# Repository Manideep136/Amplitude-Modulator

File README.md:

# Amplitude-Modulator

📌 Project Overview

This project is an Amplitude Modulator (AM) circuit designed and implemented as a PCB using KiCad.

Amplitude modulation is a technique used in communication systems where the amplitude of a high-frequency carrier signal is varied according to the amplitude of a lower-frequency message signal.

The purpose of this project is to understand the basic concept of AM and implement a simple amplitude modulation circuit using electronic components.

🎯 Objectives
Understand the basic concept of amplitude modulation.
Generate a carrier signal and message signal.
Combine the signals to produce an AM waveform.
Design the AM circuit schematic in KiCad.
Assign appropriate footprints to components.
Create a PCB layout.
Route the PCB tracks.
Perform ERC and DRC checks.
Visualize the completed PCB using KiCad 3D Viewer.
📡 What is Amplitude Modulation?

Amplitude Modulation (AM) is a modulation technique in which the amplitude of a carrier signal is changed according to the message signal, while the carrier frequency remains constant.

In simple terms:

Message Signal + Carrier Signal
              │
              ▼
       AM Modulator Circuit
              │
              ▼
          AM Output

The message signal contains the information, while the carrier signal is a higher-frequency signal used to carry that information.

⚙️ Working Principle

The amplitude modulator takes two input signals:

Message signal – the information signal.
Carrier signal – a high-frequency signal.

The modulator combines these signals and produces an amplitude-modulated output.

The basic AM equation is:

s(t) = Ac [1 + μ cos(ωm t)] cos(ωc t)

Where:

Ac = Carrier amplitude
μ = Modulation index
ωm = Message signal angular frequency
ωc = Carrier signal angular frequency

The frequency of the carrier remains constant, while its amplitude changes according to the message signal.

🧩 Components Used

The exact components depend on the circuit implementation. A typical AM modulator PCB may contain:

Reference	Component	Quantity
Q1	Transistor / Modulator Device	1
R1–R4	Resistors	As required
C1–C3	Capacitors	As required
J1	Message Signal Input	1
J2	Carrier Signal Input	1
J3	AM Output	1
VCC	DC Power Supply	1

Component values should be selected according to the actual schematic used in the project.

🔌 Inputs and Outputs
Message Input

The low-frequency information signal is connected to the message input.

Message Signal
      │
      ▼
   AM Circuit
Carrier Input

The high-frequency carrier signal is supplied to the carrier input.

Carrier Signal
      │
      ▼
   AM Circuit
AM Output

The resulting amplitude-modulated signal is available at the output connector.

Message + Carrier
       │
       ▼
 AM Modulator
       │
       ▼
   AM Output
🖥️ KiCad Design

The complete circuit was designed using KiCad.

Design Process
Create a new KiCad project.
Create the AM modulator schematic.
Add the required components.
Connect the components according to the circuit.
Add power connections.
Assign footprints.
Transfer the schematic to PCB Editor.
Place the components.
Route the PCB tracks.
Check the design using ERC.
Check the PCB using DRC.
View the final PCB using the 3D Viewer.

🔍 PCB Design Considerations

When designing the AM PCB, special attention should be given to:

Short signal paths.
Proper grounding.
Correct component placement.
Avoiding unnecessary long tracks.
Keeping the carrier signal path clean.
Proper separation of input and output signals.
Correct footprint selection.
Appropriate PCB track widths.

Since AM circuits can work with relatively higher-frequency signals, good PCB layout practices help reduce unwanted noise and interference.

🧪 Testing

After completing the PCB:

Check all component values.
Verify component orientation.
Check transistor pin configuration if a transistor is used.
Check capacitor polarity for polarized capacitors.
Verify the power supply connections.
Run ERC in KiCad.
Run DRC in KiCad.
Check the PCB for shorts.
Apply the required DC supply.
Connect the message signal.
Connect the carrier signal.
Observe the output using an oscilloscope.

The oscilloscope should show an AM waveform whose envelope follows the message signal.

📈 Modulation Index

The modulation index indicates how strongly the carrier is being modulated.

It can be calculated from the AM waveform as:

μ = (Vmax - Vmin) / (Vmax + Vmin)

Where:

Vmax = Maximum envelope amplitude
Vmin = Minimum envelope amplitude

For normal AM operation:

0 ≤ μ ≤ 1

If the modulation index becomes greater than 1, over-modulation can occur, which causes distortion.

✅ Advantages
Simple concept and easy to understand.
Useful for learning communication-system fundamentals.
Easy to observe using an oscilloscope.
Demonstrates the relationship between message and carrier signals.
Can be extended into a complete communication system.
⚠️ Limitations
AM is less power-efficient than some modern modulation techniques.
A significant amount of power can be present in the carrier.
It is susceptible to noise.
Over-modulation can cause distortion.
Practical performance depends on the circuit design and component selection.
🚀 Future Improvements

The project can be improved by adding:

Adjustable modulation depth.
Variable carrier frequency.
Signal amplification stage.
RF output stage.
LC filtering.
Audio input connector.
Oscilloscope test points.
Demodulator circuit.
Complete AM transmitter and receiver.
📚 Learning Outcomes

Through this project, I learned:

Basic principles of amplitude modulation.
Difference between message and carrier signals.
AM waveform generation.
Modulation index.
Schematic design using KiCad.
Component and footprint selection.
PCB component placement.
PCB routing.
ERC and DRC checking.
PCB testing using an oscilloscope.
🛠️ Software Used

KiCad 9.0

⚠️ Safety Notice

This project should be operated using the specified low-voltage supply and signal levels for the circuit.

Do not connect the circuit directly to mains voltage or unauthorized RF equipment. Use appropriate laboratory equipment and follow the ratings of all components.

📄 License

This project is created for educational purposes. You may modify, improve, and use the design for learning and personal electronics projects.

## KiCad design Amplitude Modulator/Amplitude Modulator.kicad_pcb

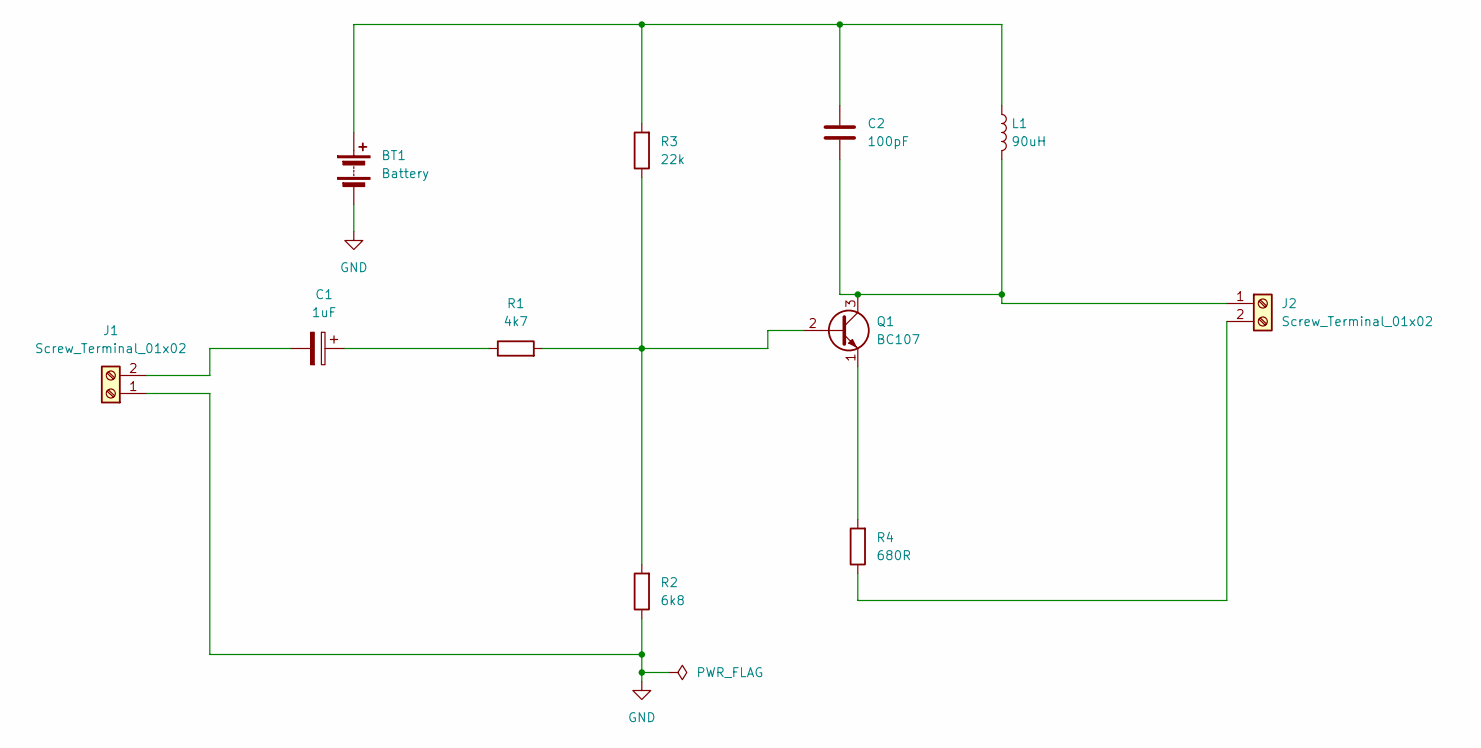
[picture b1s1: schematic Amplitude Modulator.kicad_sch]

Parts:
BT1: Battery; BatteryHolder_Keystone_3034_1x20mm
C1: 1uF; CP_Radial_D6.3mm_P2.50mm
C2: 100pF; CP_Radial_D10.0mm_P7.50mm
J1, J2: Screw_Terminal_01x02; TerminalBlock_Phoenix_MKDS-1,5-2-5.08_1x02_P5.08mm_Horizont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
L1: 90uH; Choke_EPCOS_B82722A
Q1: BC107; TO-18-3
R1: 4k7; R_Axial_DIN0411_L9.9mm_D3.6mm_P12.70mm_Horizontal
R2: 6k8; R_Axial_DIN0411_L9.9mm_D3.6mm_P12.70mm_Horizontal
R3: 22k; R_Axial_DIN0411_L9.9mm_D3.6mm_P12.70mm_Horizontal
R4: 680R; R_Axial_DIN0411_L9.9mm_D3.6mm_P25.40mm_Horizontal

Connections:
GND: BT1.2 (-), J1.1, R2.1
unnamed: BT1.1 (+), C2.1, L1.1, R3.2
unnamed: C1.1, R1.1
unnamed: C1.2, J1.2
unnamed: C2.2, J2.1, L1.2, Q1.3 (C)
unnamed: J2.2, R4.1
unnamed: Q1.2 (B), R1.2, R2.2, R3.1
unnamed: Q1.1 (E), R4.2

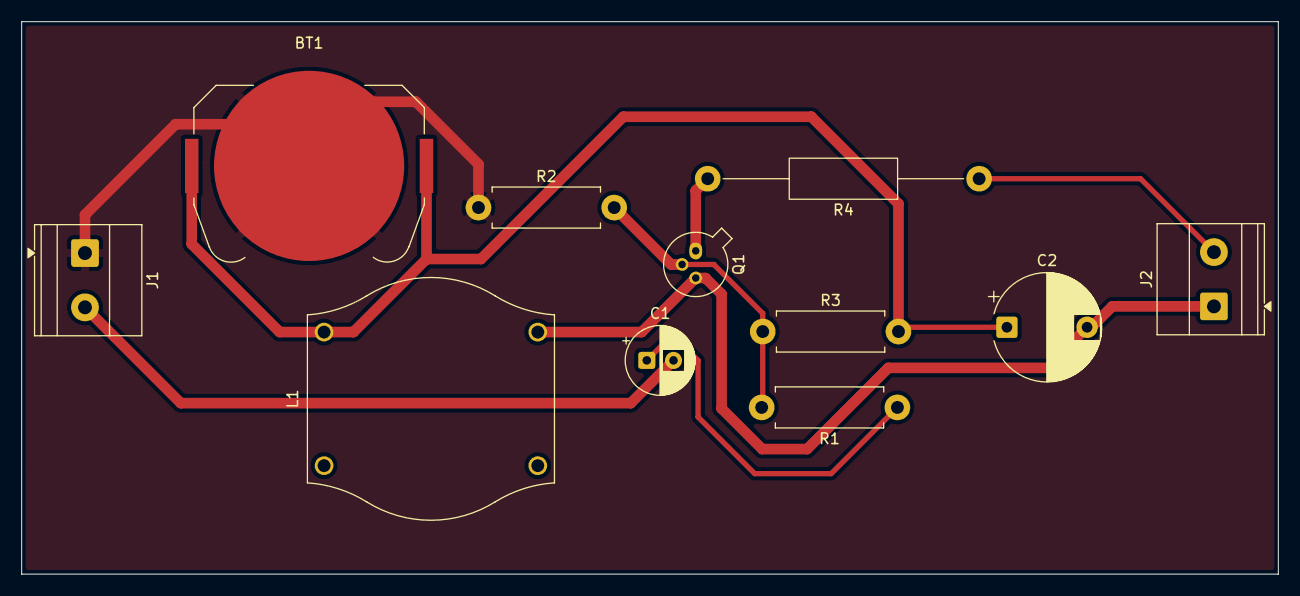
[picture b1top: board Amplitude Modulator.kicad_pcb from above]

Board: 2 copper layers, 117.6 x 51.7 mm, 11 parts (0 on the bottom side), 8 nets.
